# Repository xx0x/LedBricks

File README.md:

# LedBricks
Simple PCBs to use with LEGO®, containing LEDs to light up your creations.

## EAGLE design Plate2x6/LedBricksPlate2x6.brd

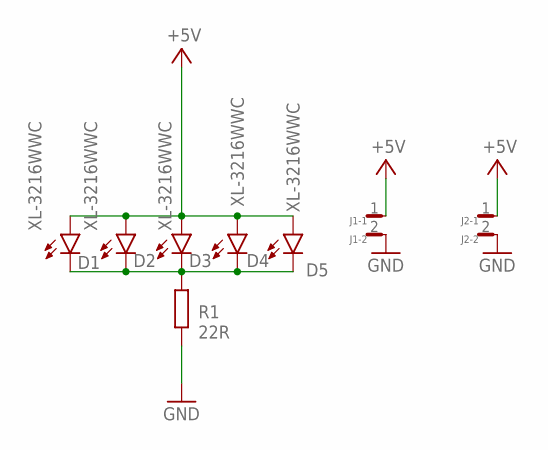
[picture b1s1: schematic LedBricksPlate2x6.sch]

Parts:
D1, D2, D3, D4, D5: XL-3216WWC; LED-1206
J1, J2: SM02B-SRSS-TB
R1: 22R; R0805

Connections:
+5V: D1.A, D2.A, D3.A, D4.A, D5.A, J1.1, J2.1
GND: J1.2, J2.2, R1.1
unnamed: D1.C, D2.C, D3.C, D4.C, D5.C, R1.2

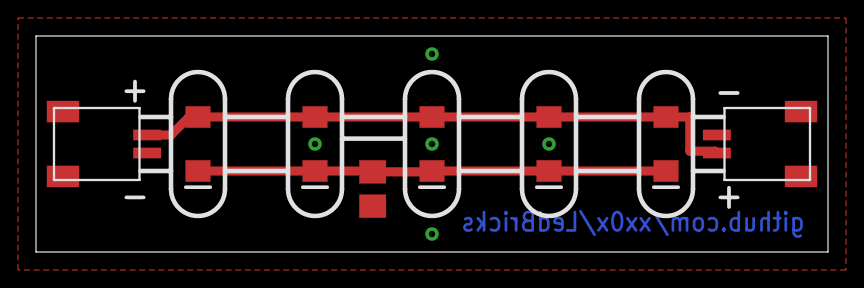
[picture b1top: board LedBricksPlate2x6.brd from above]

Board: 2 copper layers, 44.0 x 12.0 mm, 8 parts (0 on the bottom side), 3 nets.

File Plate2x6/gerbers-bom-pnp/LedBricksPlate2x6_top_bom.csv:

Comment,Designator,Footprint,LCSC Part #
22R,R1,R0805,
SM02B-SRSS-TB,J1 J2,SM02B-SRSS-TB,
XL-3216WWC,D1 D2 D3 D4 D5,LED-1206,

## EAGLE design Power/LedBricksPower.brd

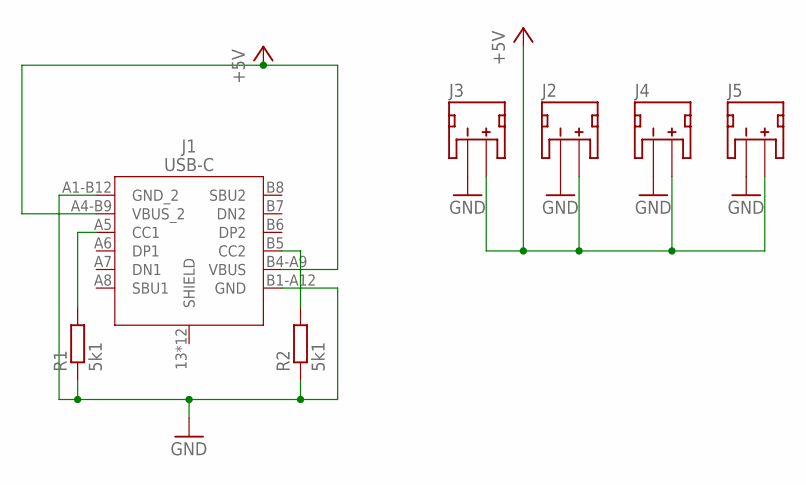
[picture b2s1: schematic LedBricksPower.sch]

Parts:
J1: USB-C
J2, J3, J4, J5: JST_2MM_MALE; JST-2-SMD
R1, R2: 5k1; R0603

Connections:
+5V: J1.A4-B9 (VBUS_2), J1.B4-A9 (VBUS), J2.2 (+), J3.2 (+), J4.2 (+), J5.2 (+)
GND: J1.A1-B12 (GND_2), J1.B1-A12 (GND), J2.1 (-), J3.1 (-), J4.1 (-), J5.1 (-), R1.1, R2.1
unnamed: J1.A5 (CC1), R1.2
unnamed: J1.B5 (CC2), R2.2

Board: 2 copper layers, 7 parts (0 on the bottom side), 4 nets, no tracks yet.

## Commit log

2023-01-14 add 2x6 plate schematics
2023-01-14 add power
2023-01-14 change connector to jst sh
2023-01-14 gerbers, pnp file

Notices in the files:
parts and their libraries:
SparkFun-LED: Licensing: Creative Commons ShareAlike 4.0 International - https://creativecommons.org/licenses/by-sa/4.0
